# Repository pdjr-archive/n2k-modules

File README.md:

# n2k-modules - a collection of NMEA 2000 hardware modules

Each module includes one or more hardware designs and an associated
collection of firmware.

| Module | Description |
|:-------|:-------------------------------------------------------|
| THR100 | Thruster module (combined switch and relay interfaces) |
| TMP108 | Temperature module |
| WIN110 | Windlass switch input interface |
| WIN120 | Windlass relay output interface |

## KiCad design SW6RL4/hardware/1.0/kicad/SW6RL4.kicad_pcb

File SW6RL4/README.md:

# SW6RL4 Generic Module

The __SW6RL4__ is a hardware design for an NMEA 2000 module which
provides generalised support for devices which require multiple
switch and sensor inputs and relay outputs.

The design offers:

* six optically-isolated 12/24VDC switch inputs;
* four analogue inputs suitable for voltage measurement (the module
  provides 5V reference and ground connections for each analogue
  input);
* four SPST relay outputs rated at 5A DC;
* LED output for power / status indication;
* 9 DIP switch configuration inputs suitable for setting a module
  instance address, etc.

The module GPIO configuration is available as simple C++ header file
[SW6RL4.h](SW6RL4.h) which firmware applications can import to
bootstrap development.

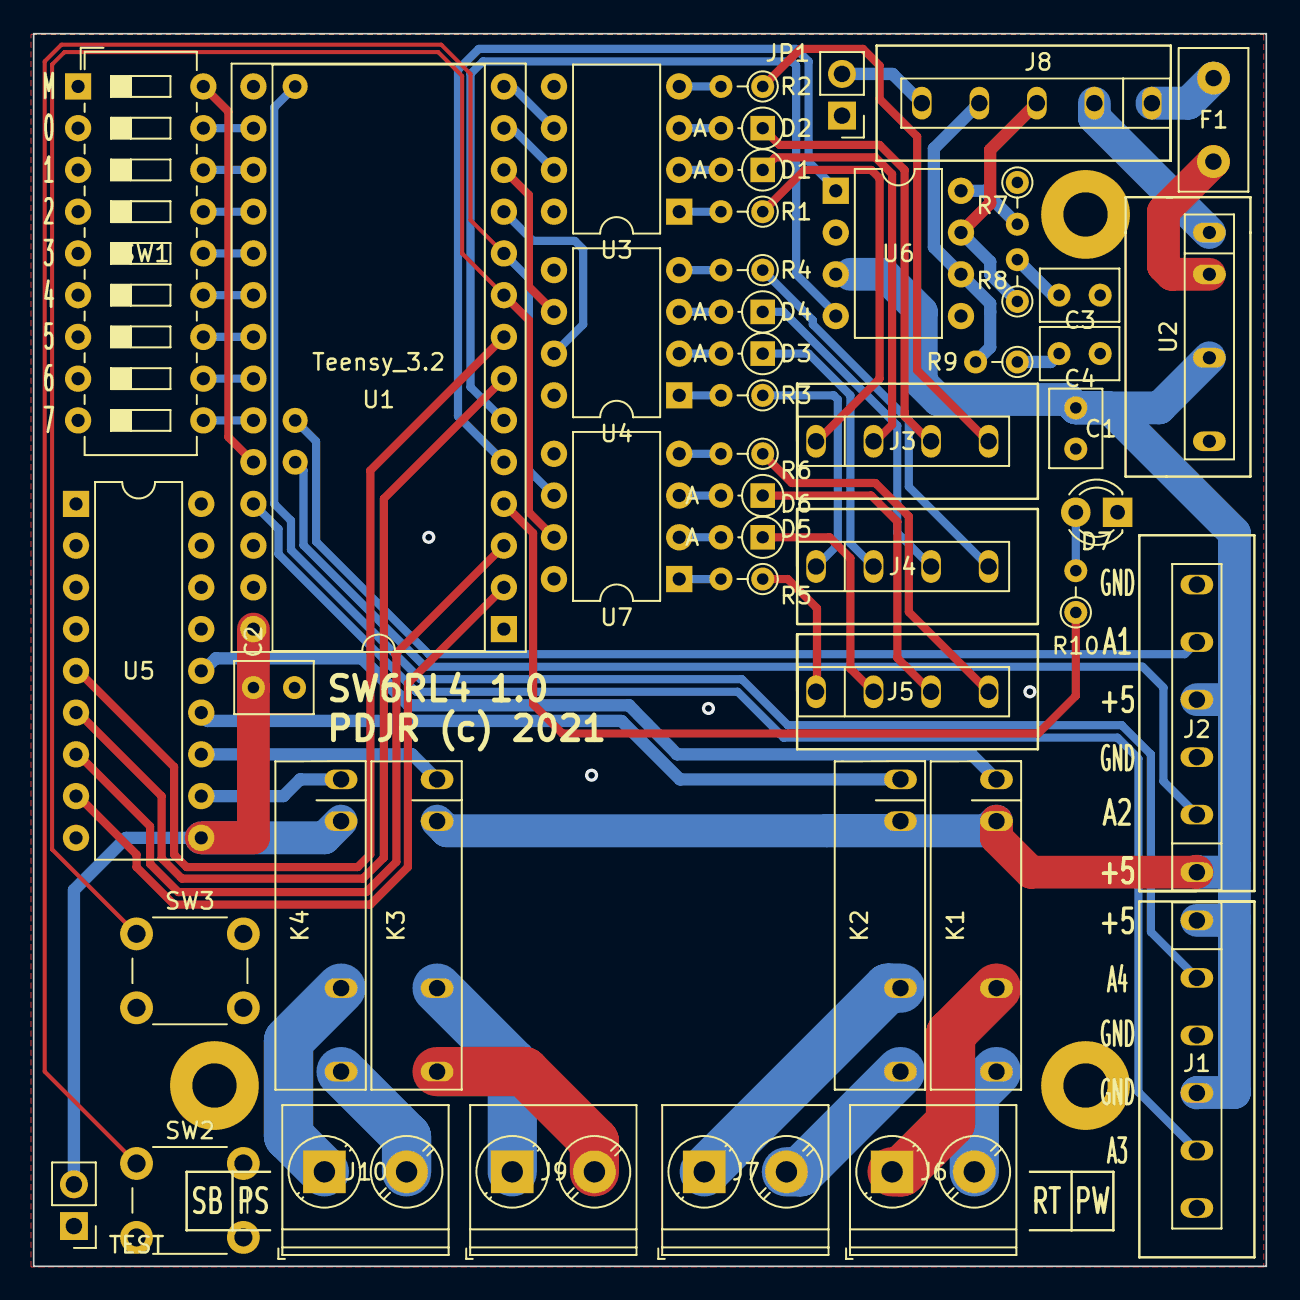
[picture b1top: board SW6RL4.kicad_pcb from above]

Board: 2 copper layers, 75.0 x 75.0 mm, 48 parts (0 on the bottom side), 74 nets.

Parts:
C1: 100nF; C_Rect_L4.6mm_W3.0mm_P2.50mm_MKS02_FKP02
C2: 100n; C_Rect_L4.6mm_W3.0mm_P2.50mm_MKS02_FKP02
C3, C4: 560p; C_Rect_L4.6mm_W3.0mm_P2.50mm_MKS02_FKP02
D1, D2, D3, D4, D5, D6: 1N4001; D_DO-34_SOD68_P2.54mm_Vertical_AnodeUp
D7: PWR; LED_D3.0mm_FlatTop
F1: 1A; Fuse_Littelfuse_395Series
J1: ANALOG_A; Phoenix-FK-MPT-6-3,5
J2: ANALOG_B; Phoenix-FK-MPT-6-3,5
J3, J5: SB1; Phoenix-FK-MPT-4-3,5
J4: SB0; Phoenix-FK-MPT-4-3,5
J6, J7, J9, J10: Screw_Terminal_01x02; TerminalBlock_Phoenix_PT-1,5-2-5.0-H_1x02_P5.00mm_Horizontal
J8: CAN; Phoenix-FK-MPT-5-3,5
JP1: SCR; PinHeader_1x02_P2.54mm_Vertical
K1, K2, K3, K4: FINDER-32.21-x300; APAN-3105
R1, R2, R3, R4, R5, R6: 1K4; R_Axial_DIN0204_L3.6mm_D1.6mm_P2.54mm_Vertical
R7: 4K7; R_Axial_DIN0204_L3.6mm_D1.6mm_P2.54mm_Vertical
R8, R9: 100R; R_Axial_DIN0204_L3.6mm_D1.6mm_P2.54mm_Vertical
R10: 200R; R_Axial_DIN0204_L3.6mm_D1.6mm_P2.54mm_Vertical
SW1: MODE_ADDRESS; SW_DIP_SPSTx09_Slide_6.7x24.42mm_W7.62mm_P2.54mm_LowProfile
SW2, SW3: SW_MEC_5E; SW_PUSH_6mm_H4.3mm
TEST: PinHeader_1x02_P2.54mm_Vertical
U1: Teensy_3.2
U2: TMR-1211; TMR-1-1211
U3, U4, U7: CNY74-2H; DIP-8_W7.62mm
U5: ULN2803A; DIP-18_W7.62mm
U6: MCP2551-I-P; DIP-8_W7.62mm

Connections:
+5V: C1.1, C2.1, J1.1, J1.4, J2.1, J2.4, K1.A2, K2.A2, K3.A2, K4.A2, TEST.2, U1.28, U2.4, U5.10, U6.3
/ADDR_0: SW1.17, U1.16
/ADDR_1: SW1.16, U1.17
/ADDR_2: SW1.15, U1.18
/ADDR_3: SW1.14, U1.19
/ADDR_4: SW1.13, U1.20
/ADDR_5: SW1.12, U1.21
/ADDR_6: SW1.11, U1.22
/ADDR_7: SW1.10, U1.23
/ANALOG_1: J2.5, U1.30
/ANALOG_2: J2.2, U1.29
/ANALOG_3: J1.5, U1.25
/ANALOG_4: J1.2, U1.31
/CAN_H: J8.3, R8.1, U6.7
/CAN_L: J8.4, R9.2, U6.6
/CAN_RX: U1.6, U6.4
/CAN_SCR: J8.5, JP1.2
/CAN_TX: U1.5, U6.1
/LED_1: R10.1, U1.4
/MODE: SW1.18, U1.24
/NET_C: J8.2, U2.1
/NET_S: F1.1, J8.1
/PUSH_1: SW2.1, U1.10, U7.6
/PUSH_2: SW3.1, U1.9, U7.7
/RELAY_1: U1.8, U5.5
/RELAY_2: U1.7, U5.6
/RELAY_3: U1.3, U5.7
/RELAY_4: U1.2, U5.8
/SWITCH_1: U1.14, U3.6
/SWITCH_2: U1.13, U3.7
/SWITCH_3: U1.12, U4.6
/SWITCH_4: U1.11, U4.7
GND: C1.2, C2.2, C3.1, C4.1, D7.1, J1.3, J1.6, J2.3, J2.6, JP1.1, R7.1, SW1.1, SW1.2, SW1.3, SW1.4, SW1.5, SW1.6, SW1.7, SW1.8, SW1.9, TEST.1, U1.1, U1.27, U2.6, U3.5, U3.8, U4.5, U4.8, U5.9, U6.2, U7.5, U7.8
unnamed: C3.2, R8.2
unnamed: C4.2, R9.1
unnamed: D1.1, J3.2
unnamed: D1.2, U3.2
unnamed: D2.1, J3.3
unnamed: D2.2, U3.3
unnamed: D3.1, J4.2
unnamed: D3.2, U4.2
unnamed: D4.1, J4.3
unnamed: D4.2, U4.3
unnamed: D5.1, J5.2
unnamed: D5.2, U7.2
unnamed: D6.1, J5.3
unnamed: D6.2, U7.3
unnamed: D7.2, R10.2
unnamed: F1.2, U2.2
unnamed: J3.1, R1.1
unnamed: J3.4, R2.1
unnamed: J4.1, R3.1
unnamed: J4.4, R4.1
unnamed: J5.1, R5.1
unnamed: J5.4, R6.1
unnamed: J6.1, K1.14
unnamed: J6.2, K1.11
unnamed: J7.1, K2.14
unnamed: J7.2, K2.11
unnamed: J9.1, K3.14
unnamed: J9.2, K3.11
unnamed: J10.1, K4.14
unnamed: J10.2, K4.11
unnamed: K1.A1, U5.14
unnamed: K2.A1, U5.13
unnamed: K3.A1, U5.12
unnamed: K4.A1, U5.11
unnamed: R1.2, U3.1
unnamed: R2.2, U3.4
unnamed: R3.2, U4.1
unnamed: R4.2, U4.4
unnamed: R5.2, U7.1
unnamed: R6.2, U7.4
unnamed: R7.2, U6.8

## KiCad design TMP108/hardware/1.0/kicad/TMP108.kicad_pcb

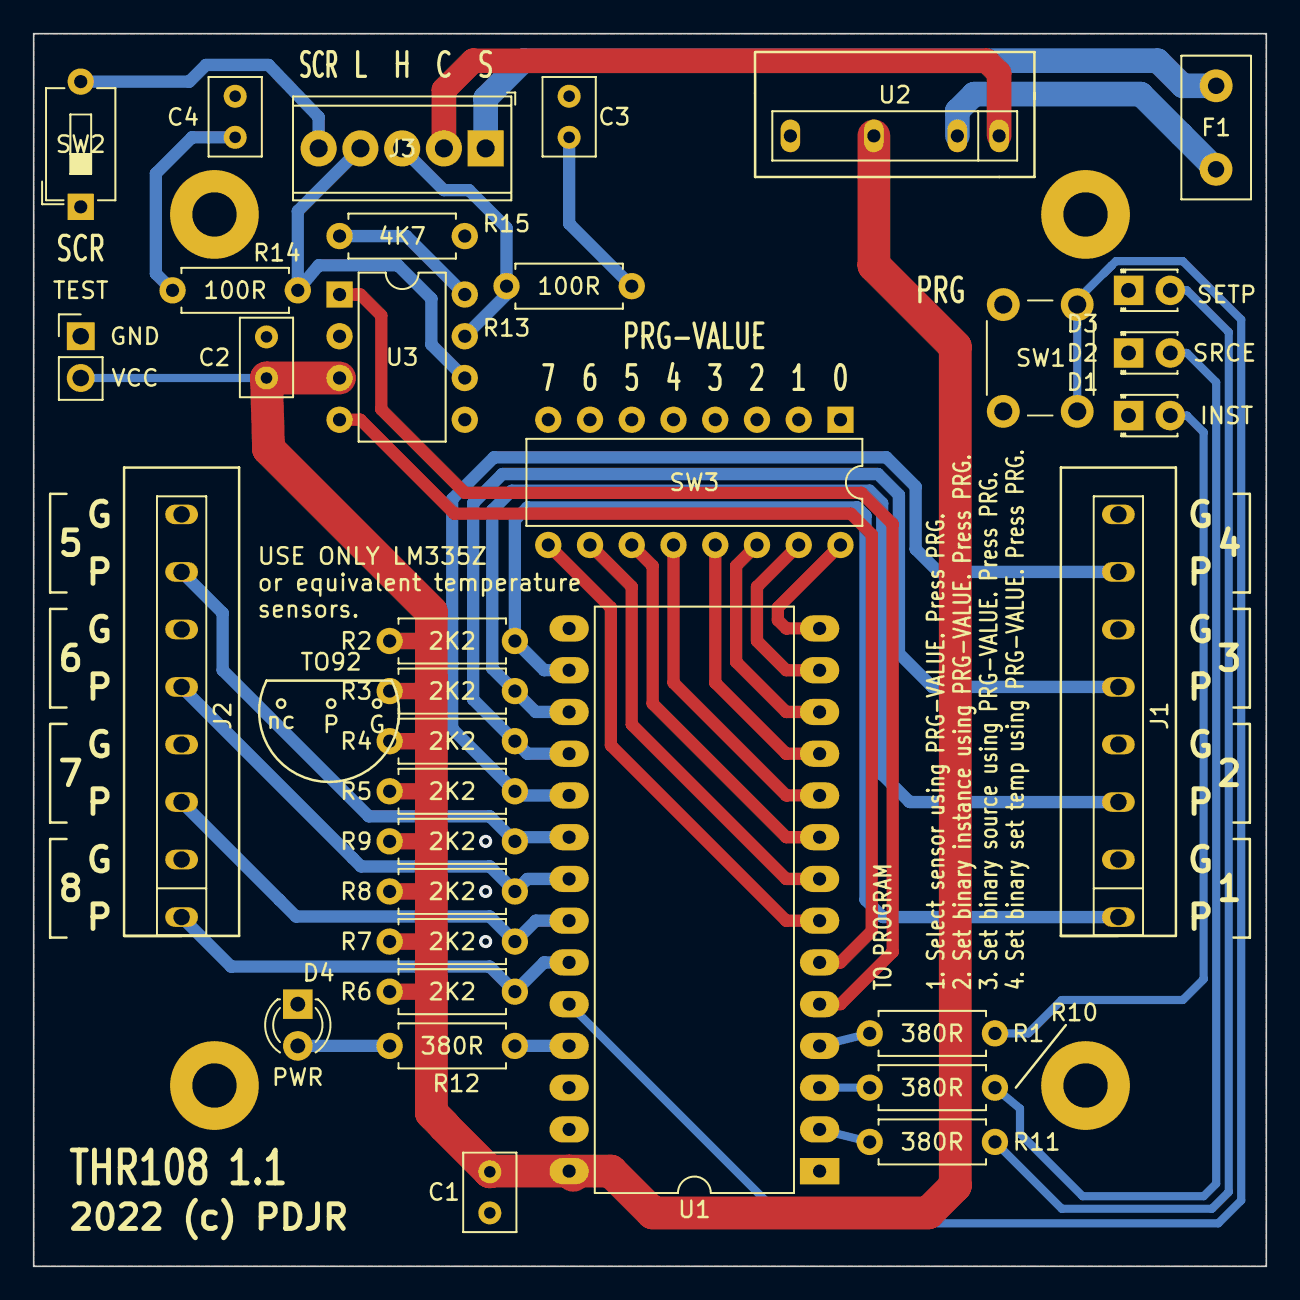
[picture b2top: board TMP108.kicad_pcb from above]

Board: 2 copper layers, 75.0 x 75.0 mm, 34 parts (0 on the bottom side), 38 nets.

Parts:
C1: 100nF; C_Rect_L4.6mm_W3.0mm_P2.50mm_MKS02_FKP02
C2: 100n; C_Rect_L4.6mm_W3.0mm_P2.50mm_MKS02_FKP02
C3, C4: 560p; C_Rect_L4.6mm_W3.0mm_P2.50mm_MKS02_FKP02
D1: INST; LED_D1.8mm_W3.3mm_H2.4mm
D2: SRCE; LED_D1.8mm_W3.3mm_H2.4mm
D3: SETP; LED_D1.8mm_W3.3mm_H2.4mm
D4: PWR; LED_D3.0mm_FlatTop
F1: 1A; Fuse_Littelfuse_395Series
J1, J2: Screw_Terminal_01x08; Phoenix-FK-MPT-8-3,5
J3: CAN; TerminalBlock_Phoenix_MPT-0,5-5-2.54_1x05_P2.54mm_Horizontal
R1, R10, R11, R12: 380R; R_Axial_DIN0207_L6.3mm_D2.5mm_P7.62mm_Horizontal
R2, R3, R4, R5, R6, R7, R8, R9: 2K2; R_Axial_DIN0207_L6.3mm_D2.5mm_P7.62mm_Horizontal
R13, R14: 100R; R_Axial_DIN0207_L6.3mm_D2.5mm_P7.62mm_Horizontal
R15: 4K7; R_Axial_DIN0207_L6.3mm_D2.5mm_P7.62mm_Horizontal
SW1: PRG; SW_PUSH_6mm_H4.3mm
SW2: SCR; SW_DIP_SPSTx01_Slide_6.7x4.1mm_W7.62mm_P2.54mm_LowProfile
SW3: PRG-VALUE; DIP-16_W7.62mm
TEST: PinHeader_1x02_P2.54mm_Vertical
U1: Teensy_3.2; DIP-28_W15.24mm_LongPads
U2: TMR-1211; TMR-1-1211
U3: MCP2551-I-P; DIP-8_W7.62mm

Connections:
+5V: C1.1, C2.1, R2.2, R3.2, R4.2, R5.2, R6.2, R7.2, R8.2, R9.2, TEST.2, U1.28, U2.4, U3.3
/ADDR_0: SW3.16, U1.14
/ADDR_1: SW3.15, U1.13
/ADDR_2: SW3.14, U1.12
/ADDR_3: SW3.13, U1.11
/ADDR_4: SW3.12, U1.10
/ADDR_5: SW3.11, U1.9
/ADDR_6: SW3.10, U1.8
/ADDR_7: SW3.9, U1.7
/CAN_H: J3.3, R13.1, U3.7
/CAN_L: J3.4, R14.2, U3.6
/CAN_RX: U1.6, U3.4
/CAN_SCR: J3.5, SW2.2
/CAN_TX: U1.5, U3.1
/LED_INSTANCE: R1.1, U1.4
/LED_PWR: R12.1, U1.25
/LED_SETPOINT: R11.1, U1.2
/LED_SOURCE: R10.1, U1.3
/NET_C: J3.2, U2.1
/NET_S: F1.1, J3.1
/SENSOR_T0: J1.1, R2.1, U1.16
/SENSOR_T1: J1.3, R3.1, U1.17
/SENSOR_T2: J1.5, R4.1, U1.18
/SENSOR_T3: J1.7, R5.1, U1.19
/SENSOR_T4: J2.7, R9.1, U1.20
/SENSOR_T5: J2.5, R8.1, U1.21
/SENSOR_T6: J2.3, R7.1, U1.22
/SENSOR_T7: J2.1, R6.1, U1.23
GND: C1.2, C2.2, C3.1, C4.1, D1.1, D2.1, D3.1, D4.1, J1.2, J1.4, J1.6, J1.8, J2.2, J2.4, J2.6, J2.8, R15.1, SW1.1, SW2.1, SW3.1, SW3.2, SW3.3, SW3.4, SW3.5, SW3.6, SW3.7, SW3.8, TEST.1, U1.1, U1.27, U2.6, U3.2
unnamed: C3.2, R13.2
unnamed: C4.2, R14.1
unnamed: D1.2, R1.2
unnamed: D2.2, R10.2
unnamed: D3.2, R11.2
unnamed: D4.2, R12.2
unnamed: F1.2, U2.2
unnamed: R15.2, U3.8
unnamed: SW1.2, U1.24

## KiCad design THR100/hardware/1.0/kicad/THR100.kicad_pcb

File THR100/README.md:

# THR100 Thruster Module

The __THR100 Thruster Module__ is an NMEA 2000 module which implements
the NMEA Thruster Network Messages protocol described in this
[Technical Bulletin](https://www.nmea.org/Assets/20190613%20thruster%20amendment%20128006,%20128007,%20128008.pdf).

The __THR100__ module is uses the
[SW6RL4](https://github.com/preeve9534/n2k-modules/SW4RL4/#README.md)
hardware platform and can operate as either a switch interface or a
relay interface dependent upon the setting of the SW6RL4's MODE DIP
switch.

In switch interface mode the __THR100__ accepts command inputs from
physical switches and potentiometers and transmits these commands over
the NMEA bus to a remote thruster.
The address of the remote thruster to which commands are sent is
configured by the SW6RL4 ADDRESS DIP switch.

In relay interface mode the __THR100__ listens on the NMEA bus for
commands and responds by operating physical relays which can be
wired to operate a connected thruster.
The address of the thruster is configured by the SW6RL4 ADDRESS DIP
switch.

## THR100 acting as a switch interface

When acting as a switch interface the __THR100__ module supports
connection of the following inputs.

| STARBOARD | Direction control | SPST momentary | Required |
| PORT      | Direction control | SPST momentary | Required |
| POWER     | Thruster enable   | SPST           | Optional |
| RETRACT   | Retract thruster  | SPST           | Optional |
| SPEED     | Speed (0-100%)    | Potentiometer  | Optional |
| AZIMUTH   | Angle             | Potentiometer  | Optional |

Input signals are decoded and transmitted to the remote thruster
addressed by the ADDRESS DIP switch.

The following relay outputs of the SW6RL4 are 

## THR100 acting as a relay interface

When acting as a relay interface the __THR100__ module listens on the
NMEA 2000 bus for a PGN ?????? Group Update Control message using
PGN128006 Thruster Control Status which addresses the thruster
identifier set by the PCB DIL switch.

At the present time the module will only react to commands for
direction control and responds by operating either PS or SB relays
dependent upon received commands.
For continuous operation of a relay a continuous stream of control
messages must be received: if the control stream dries up, then
relay ouputs are switched off.

To cater for the needs of some hydraulic systems which require
operation of a load-sense valve when there is a call for any
thruster operation, a __THR100__ in operating mode can be set to
operate both its output relays whenever it receives an operating
command of any sort allowing eithr the PORT or STARBOARD relay to
be used to operate load-sense.

__THR100__ modules communicate using the NMEA Thruster Network Messages
protocol described in this
[Technical Bulletin](https://www.nmea.org/Assets/20190613%20thruster%20amendment%20128006,%20128007,%20128008.pdf).

A simple installation controlling a single electrical thruster from
one helm location will require two __THR100__ modules: one installed
at the thruster and set to operate mode and another installed at the
helm and set to control mode.

A hydraulic installation may require an additional __THR100__ (set
to operate mode with common enabled) to operate a hydraulic system's
load-sense valve.

__THR100__ connects to a host NMEA bus by a standard M12 5-pin circular
connector and is powered directly from the NMEA bus.
The module has an NMEA LEN of 0.5 in control mode and 1.5 in operating
mode.

A diagnostic LED confirms thruster connection and module operating
status.

## About the module

Figure 1 illustrates the appearance of the module with the cover in
place and with the cover removed.

The top cover includes the NMEA bus connector (1) and the PWR status
LED (2).
The cover is penetrated by two cable glands (3) which allow passage
switch or relay connector cables.

The top cover is released by pinching at (A) after which it can be
lifted away from the the base to expose the printed circuit board (PCB).
The PCB has sensor wire terminals (4), a programme switch (5), a
configuration DIL switch (6) and three configuration state LEDs (7).
A jumper (8) allows connection of the NMEA cable shield to the module
ground.

### (1) NMEA bus connector

The module uses an M12, circular, female, 5-pin industrial connector
for NMEA connection.
An N2K standard-compliant drop cable will allow the module to be
connected to a host NMEA bus through a T-connector.

### (2) PWR status LED

The PWR status LED is modulated to indicate operating status.

| Module mode | LED   | Illumination state         | Meaning |
|:------------|:------|:---------------------------|:--------|
| CONTROL     | PWR   | Continuous slow flashing   | The module is attempting to establish a connection with the configured thruster. |
|             | " "   | Steady                     | The module is connected to the configured thruster. |
|             | " "   | Continuous rapid occulting | The module is transmitting thruster commands. |
| OPERATING   | PWR   | Continuous                 | The module is powered. |
|             | " "   | Occasional occult          | The module is transmitting status reports. |
|             | PSRLY | Steady                     | The PS relay is ON. |
|             | SBRLY | Steady                     | The SB relay is ON. |

### (3) Cable glands

Two 6mm cable glands allow passage of switch and indicator connection
cables.

### (4) Sensor wire terminals

Two 8-pin terminal blocks allow the connection of up to eight two-wire
LM335Z temperature sensors, numbered 0 through 7. Each sensor requires
a two-wire connection to its respective positive (P) and ground (G)
pins; the LM335Z calibration pin is not used.

| Terminal | Function                        |
|:--------:|:--------------------------------|
| [0..7]-P | Positive connection to sensor   |
| [0..7]-G | Ground connection to sensor     |

DO NOT connect resistive or milliamp temperature sensors to these
terminal inputs.

### (5) Programme switch

The PRG programme switch is a momentary action push button which is
used together with DIL switch (6) to configure each connected sensor
channel's NMEA properties.

### (6) DIL switch

The DIL switch allows the selection of a sensor channel which is to be
programmed and the entry of binary-encoded sensor configuration data.
The switch consists of eight small slide switches labelled one through
eight. 

### (7) Programme state LEDs

There are three LEDs labelled INST, SRCE and SETP which are used to
indicate what data has been entered and what is required whilst a sensor
channel is being configured.

During normal module operation these LEDs will all be switched off.

### (8) SCR switch

With the switch closed the NMEA cable shield is connected to the module
ground plane.

## Temperature sensors

The TSENSE module supports a maximum of eight LM335Z or equivalent
temperature sensor IC.
Other types of temperature sensor cannot be used and connecting them
to a TSENSE module will almost certainly damage the module beyond
repair.

LM335Z-based temperature sensors are commercially available (for
example Victron ) or you can easily make your own sensor.

The LM335Z sensor IC is packaged in a TO-92 housing and has the
following pin layout.

Pin 1 - calibrate (not used by TSENSE)
Pin 2 - ground (G)
Pin 3 - supply (P)

### Making a bolt-on temperature sensor

You will require an LM335Z IC, a length of two-core cable with 0.5mm2
conductors, a 10mm2 ring terminal with a hole size that suits your
mounting needs and a minimum 10mm2 cable capacity and some silicone
sealer or potting compound.

1. Remove the calibrate pin from the LM335Z by cutting or breaking it
   off as close to the IC body as possible.

2. Solder an appropriate length of two-core cable to IC pins G and P.
   Make sure you can identify which pin connects to which cable core!
   Insulate the exposed connection is some way, perhaps using small
   diameter heat-shrink sleeving around each connection.

3. Fill the cable-entry port of the ring terminal with silicone-sealant
   and coat the LM335Z with sealant as well.
   Try to avoid air bubbles.

4. Fully immerse the LM335Z in the ring-terminal cable-entry port so
   that the electrical connections are completely embedded in the
   sealant and making sure that they do not touch the ring-terminal
   body.

5. Allow the sealant to fully cure.

Ordinary silicone-sealant and potting compounds are not wonderful
conductors of heat so it is good to keep the volume of these low.
Thermally conductive silicone-sealant and potting compounds perform
better, but are expensive.

## Installing and configuring the module

### Removing and replacing the module cover

The following procedures require you to remove the module cover in
order to gain access to PCB mounted terminals and switches.

To remove the module cover pinch firmly at the centre of the top and
botton edges and pull away from the base.
The NMEA connector is wired internally to the PCB with a 150mm long
cable which you should be careful not to strain excessively.
The length of cable  should allow you to conveniantly position the
cover to one side of the module base so that the PCB can be easily
accessed.
   
To replace the module cover arrange the NMEA connector cable so that
it will not be trapped between base and cover and push the cover onto
the base until it clicks in place.   

### Installing the module

1. Position the module so that you are able to connect the associated
   temperature sensors and NMEA drop-cable without excessive cable
   runs.
   Ensure that in your chosen position you are able to remove the
   module's top cover and can easily access the PCB terminals and
   switches.

2. Fix the module in your chosen location using appropriate fasteners.

### Connecting the module to the host NMEA bus

You will require a T-connector or an unused tap on a multi-drop
connector to provide a drop-cable connection point on host NMEA bus.

1. Connect an NMEA drop-cable between between the host NMEA bus and the
   module's NMEA connector.
   The module's power LED will illuminate to indicate that the module
   has power.

### Connecting temperature sensors

1. Disconnect the module NMEA cable or otherwise power down the host
   NMEA bus.

2. Remove the module cover.
   
3. Thread a temperature sensor cable through one of the entry glands
   in the module cover and connect to an unused terminal pair on the
   PCB.
   Use the G terminal of each terminal pair for the sensor ground and
   the corresponding P terminal for the sensor power supply.

   Repeat this step for each temperature sensor you wish to connect.

4. Reconnect the module NMEA cable or power-up the host NMEA bus.
   
5. Make a note of the purpose of each newly connected sensor in the
   "Comment" column of the installation table on page NNN.

## Configuring a sensor connection

You can configure a sensor connection before or after the connection
of a temperature sensor.

For the module to operate correctly each sensor connection must be
assigned an NMEA instance address, a code which describes the type of
data source associated with the temperature reading and an alarm
temperature or set point.

### Preparing for configuration

For each sensor recorded in the installation table on page NNN, insert
a value into the "Instance", "Source" and "Set-point" columns that
reflects your installation requirements and satisfies the following
constraints.

INSTANCE. The value you choose must be in the range 0 through 255 and
must be a unique identifier for each temperature sensor across the
vessel's entire NMEA installation.
The value 255 is used to indicate that a sensor connection is disabled.

SOURCE. The value you choose must be in the range 0 through 255 and
should be selected from the table included as "Annex 1: NMEA
temperature source codes".
Some standard values are defined in NMEA and will either be appropriate
or should be avoided.

SET-POINT. The value you choose must be in the range 0 through 255 and
should specify a set-point or alarm temperature in degrees Celsius.
Value below 100 are considered to be below zero Celsius, values above
100 are considered to be above zero Celsius and the value 100 specifies
0 Celsius.
Thus, the value 53 says "-53 Celsius", 147 says "+47 Celsius".

### Programming the module

The values you have defined above are programmed into the module by
setting up the required value as a binary-encoded number on the module
DIL switch and then pressing PRG to commit the DIL switch value to
the module configuration.

The programming sequence is: (1) select sensor to be programmed; (2)
enter instance; (3) enter state; (4) enter set-point.

Let us imagine we have the following temperature sensor settings:

Sensor id: 0
Instance:  0
Source:    11 (Gearbox temperature)
Set point: 85C

We begin programming by selecting the sensor we wish to configure on
the DIL switch.
The left-most switch corresponds to sensor 0, the right-most switch
to sensor 7.
We are programming sensor 0, so we set the DIL switch to [ON-OFF-OFF-OFF-OFF-OFF-OFF-OFF]
and then press PRG.

If our entry is accepted then the INST LED will flash to indicate that
the module is awaiting entry of a sensor instance value.
At this point, we have 20 seconds in which to set up the requested
instance value on the DIL switch and press PRG to confirm the entry.

We are setting an instance value of 0, so we set the DIL switch to
[OFF-OFF-OFF-OFF-OFF-OFF-OFF-OFF] and press PRG.

If our entry is accepted, then the INST LED will become steadily
illuminated and the SRCE LED will begin to flash, requesting entry of a
source value within a new 20s timeout period.

We are setting a source value of 11, so we set the DIL switch to
[OFF-OFF-OFF-OFF-ON-OFF-ON-ON] and press PRG.

If our entry is accepted then the SRCE LED will become steadily
illuminated and the SETP LED will begin to flash, requesting entry of a
set-point / alarm value within a new 20s timeout period.

We are setting a set-point value of 83, so we set the DIL switch to
[OFF-ON-OFF-ON-OFF-ON-OFF-ON] and press PRG.

If our entry is accepted then the INST, SRCE and SETP LEDs will flash
three times to indicate that all enries have been accepted and the
configuration has been saved to the module's EEPROM.

The protocol described above can be repeated to programme another
sensor channel or to amend an incorrect or inappropriate existing
entry.

If an error is made in the programming sequence or the 20s timeout
expires before an entry is made, then the all LEDS will extinquish and
the programming sequence must be restarted with the selection of the
sensor to be programmed.

## NMEA 2000 output

As soon as a temperature sensor has been programmed the module will
commence transmitting the sensor's temperature reading onto the host
NMEA bus.

The module issues the following control message types in response to
signals on the switch inputs.

| PGN    | Message name                      | Comment               |
|:-------|:----------------------------------|:----------------------|
| 126208 | Command Group Function            | 250ms transmition rate|

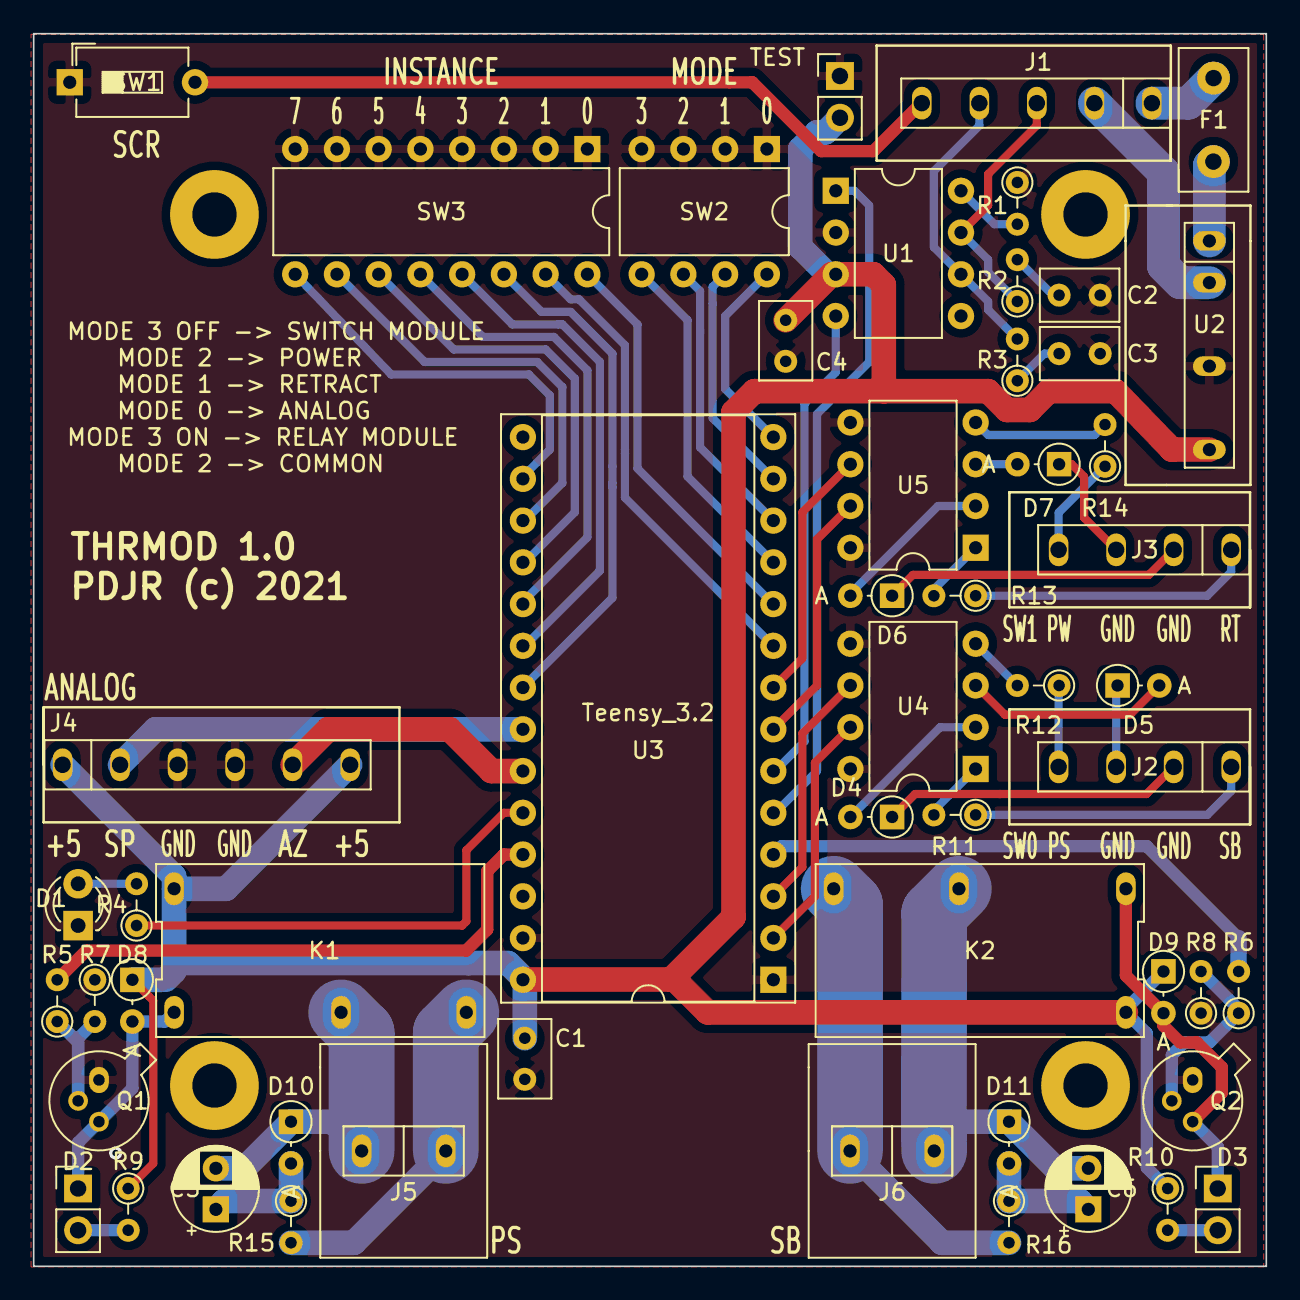
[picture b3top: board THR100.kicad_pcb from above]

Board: 2 copper layers, 75.0 x 75.0 mm, 53 parts (0 on the bottom side), 63 nets.

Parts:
C1: 100n; C_Rect_L4.6mm_W3.0mm_P2.50mm_MKS02_FKP02
C2, C3: 560p; C_Rect_L4.6mm_W3.0mm_P2.50mm_MKS02_FKP02
C4: 100nF; C_Rect_L4.6mm_W3.0mm_P2.50mm_MKS02_FKP02
C5, C6: 33n; CP_Radial_D5.0mm_P2.50mm
D1: PWR; LED_D3.0mm_FlatTop
D2, D3: L-1334SRT; PinHeader_1x02_P2.54mm_Vertical
D4, D5, D6, D7: 1N4001; D_DO-34_SOD68_P2.54mm_Vertical_AnodeUp
D8, D9: 1N4007; D_DO-34_SOD68_P2.54mm_Vertical_AnodeUp
D10, D11: D_TVS; D_DO-34_SOD68_P2.54mm_Vertical_AnodeUp
F1: 1A; Fuse_Littelfuse_395Series
J1: CAN; Phoenix-FK-MPT-5-3,5
J2: SB0; Phoenix-FK-MPT-4-3,5
J3: SB1; Phoenix-FK-MPT-4-3,5
J4: ANALOG; Phoenix-FK-MPT-6-3,5
J5, J6: Screw_Terminal_01x02; WUERTH_2015_5.08_x2
K1, K2: FINDER-32.21-x300; PCH-105L2MH
Q1, Q2: NTE123A; TO-18-3
R1, R5, R6, R7, R8: 4K7; R_Axial_DIN0204_L3.6mm_D1.6mm_P2.54mm_Vertical
R2, R3: 100R; R_Axial_DIN0204_L3.6mm_D1.6mm_P2.54mm_Vertical
R4, R9, R10: 200R; R_Axial_DIN0204_L3.6mm_D1.6mm_P2.54mm_Vertical
R11, R12, R13, R14: 1K4; R_Axial_DIN0204_L3.6mm_D1.6mm_P2.54mm_Vertical
R15, R16: 43R; R_Axial_DIN0204_L3.6mm_D1.6mm_P2.54mm_Vertical
SW1: SCR; SW_DIP_SPSTx01_Slide_6.7x4.1mm_W7.62mm_P2.54mm_LowProfile
SW2: MODE; DIP-8_W7.62mm
SW3: INSTANCE; DIP-16_W7.62mm
TEST: PinHeader_1x02_P2.54mm_Vertical
U1: MCP2551-I-P; DIP-8_W7.62mm
U2: TMR-1-1211
U3: Teensy_3.2; DIP-28_W15.24mm_Socket
U4, U5: CNY74-2H; DIP-8_W7.62mm

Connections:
+5V: C1.1, C4.1, D8.1, D9.1, J4.1, J4.6, K1.A2, K2.A2, R9.1, R10.1, TEST.2, U1.3, U2.6, U3.28
/ADDR_0: SW3.16, U3.10
/ADDR_1: SW3.15, U3.9
/ADDR_2: SW3.14, U3.21
/ADDR_3: SW3.13, U3.20
/ADDR_4: SW3.12, U3.19
/ADDR_5: SW3.11, U3.18
/ADDR_6: SW3.10, U3.17
/ADDR_7: SW3.9, U3.16
/AZIMUTH: J4.5, U3.23
/CAN_H: J1.3, R2.1, U1.7
/CAN_L: J1.4, R3.2, U1.6
/CAN_RX: U1.4, U3.6
/CAN_SCR: J1.5, SW1.2
/CAN_TX: U1.1, U3.5
/LED_PWR: R4.1, U3.24
/MODE_ADDR_0: SW2.8, U3.14
/MODE_ADDR_1: SW2.7, U3.13
/MODE_ADDR_2: SW2.6, U3.12
/MODE_ADDR_3: SW2.5, U3.11
/NET_C: J1.2, U2.2
/NET_S: F1.1, J1.1
/PS_CMD: U3.3, U4.6
/PS_CO: C5.2, D10.1, J5.1, K1.11
/PS_G: D5.1, J2.3
/PS_NO: J5.2, K1.14, R15.2
/PS_P: J2.4, R12.1
/PS_RLY: R5.2, U3.25
/PW_CMD: U3.8, U5.6
/PW_G: D7.1, J3.3
/PW_P: J3.4, R14.1
/RT_CMD: U3.7, U5.7
/RT_G: D6.1, J3.2
/RT_P: J3.1, R13.1
/SB-NO: J6.1, K2.14, R16.2
/SB_CMD: U3.2, U4.7
/SB_CO: C6.2, D11.1, J6.2, K2.11
/SB_G: D4.1, J2.2
/SB_P: J2.1, R11.1
/SB_RLY: R6.2, U3.4
/SPEED: J4.2, U3.22
GND: C1.2, C2.1, C3.1, C4.2, D1.1, J4.3, J4.4, Q1.1, Q2.1, R1.1, R7.1, R8.1, SW1.1, SW2.1, SW2.2, SW2.3, SW2.4, SW3.1, SW3.2, SW3.3, SW3.4, SW3.5, SW3.6, SW3.7, SW3.8, TEST.1, U1.2, U2.4, U3.1, U3.27, U4.5, U4.8, U5.5, U5.8
unnamed: C2.2, R2.2
unnamed: C3.2, R3.1
unnamed: C5.1, D10.2, R15.1
unnamed: C6.1, D11.2, R16.1
unnamed: D1.2, R4.2
unnamed: D2.1, D8.2, K1.A1, Q1.3
unnamed: D2.2, R9.2
unnamed: D3.1, D9.2, K2.A1, Q2.3
unnamed: D3.2, R10.2
unnamed: D4.2, U4.2
unnamed: D5.2, U4.3
unnamed: D6.2, U5.2
unnamed: D7.2, U5.3
unnamed: F1.2, U2.1
unnamed: Q1.2, R5.1, R7.2
unnamed: Q2.2, R6.1, R8.2
unnamed: R1.2, U1.8
unnamed: R11.2, U4.1
unnamed: R12.2, U4.4
unnamed: R13.2, U5.1
unnamed: R14.2, U5.4

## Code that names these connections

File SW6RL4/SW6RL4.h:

#define GPIO_MODE 22
#define GPIO_ADDRESS_0 14
#define GPIO_ADDRESS_1 15
#define GPIO_ADDRESS_2 16
#define GPIO_ADDRESS_3 17
#define GPIO_ADDRESS_4 18
#define GPIO_ADDRESS_5 19
#define GPIO_ADDRESS_6 20
#define GPIO_ADDRESS_7 21
#define GPIO_ANALOG_1 A11
#define GPIO_ANALOG_2 A10
#define GPIO_ANALOG_3 A9
#define GPIO_ANALOG_4 A14
#define GPIO_SWITCH_1 12
#define GPIO_SWITCH_2 11
#define GPIO_SWITCH_3 10
#define GPIO_SWITCH_4 9
#define GPIO_SWITCH_5 8
#define GPIO_SWITCH_6 7
#define GPIO_RELAY_1 6
#define GPIO_RELAY_2 5
#define GPIO_RELAY_3 1
#define GPIO_RELAY_4 0
#define GPIO_BOARD_LED 13
#define GPIO_LED_1 2

#define GPIO_PUSH_1 GPIO_SWITCH_5
#define GPIO_PUSH_2 GPIO_SWITCH_6


#define GPIO_DIGITAL_INPUT_PINS { GPIO_MODE, GPIO_ADDRESS_0, GPIO_ADDRESS_1, GPIO_ADDRESS_2, GPIO_ADDRESS_3, GPIO_ADDRESS_4, GPIO_ADDRESS_5, GPIO_ADDRESS_6, GPIO_ADDRESS_7, GPIO_SWITCH_1, GPIO_SWITCH_2, GPIO_SWITCH_3, GPIO_SWITCH_4, GPIO_SWITCH_5, GPIO_SWITCH_6 }
#define GPIO_DIGITAL_OUTPUT_PINS { GPIO_RELAY_1, GPIO_RELAY_2, GPIO_RELAY_3, GPIO_RELAY_4, GPIO_BOARD_LED, GPIO_LED_1 }
#define GPIO_ADDRESS_PINS { GPIO_ADDRESS_0, GPIO_ADDRESS_1, GPIO_ADDRESS_2, GPIO_ADDRESS_3, GPIO_ADDRESS_4, GPIO_ADDRESS_5, GPIO_ADDRESS_6, GPIO_ADDRESS_7 }
#define GPIO_ANALOG_PINS { GPIO_ANALOG_1, GPIO_ANALOG_2, GPIO_ANALOG_3, GPIO_ANALOG_4 }

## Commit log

2021-05-09 First upload after refactor of ankreo project.
2021-05-10 Add installation folder
2021-05-11 Add azimuth support
2021-05-13 Add switch inputs
2021-05-14 PCB tweaks
2021-05-19 Add generic hardware design and refactor
2021-05-23 Big refactor for new board
2021-05-24 Refactor for generic module
2021-07-16 Change resistors to 1/4W
2022-06-05 Typos.
2022-06-06 README tweaks.
2022-06-06 Add SID counter
2022-06-06 TMP108 refactor
2022-06-06 Correct debug format error.
2022-06-06 Drop buggy ADC library
2022-12-20 Relay

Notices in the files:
SW6RL4/hardware/1.0/kicad/SW6RL4.kicad_pcb:
PDJR (c) 2021
